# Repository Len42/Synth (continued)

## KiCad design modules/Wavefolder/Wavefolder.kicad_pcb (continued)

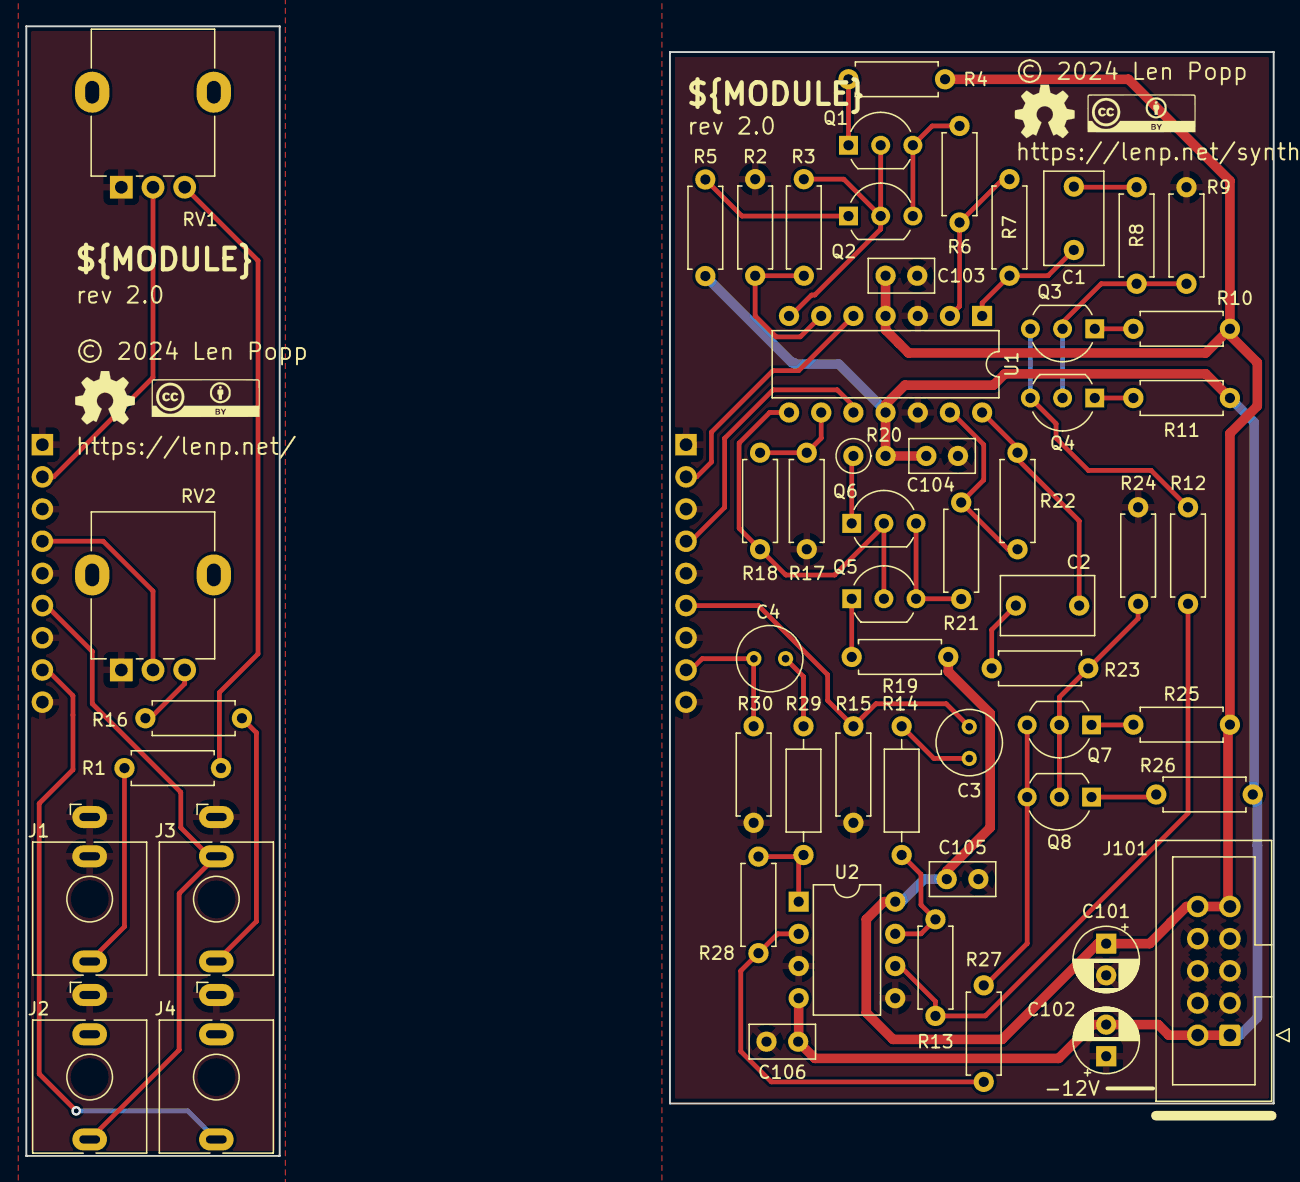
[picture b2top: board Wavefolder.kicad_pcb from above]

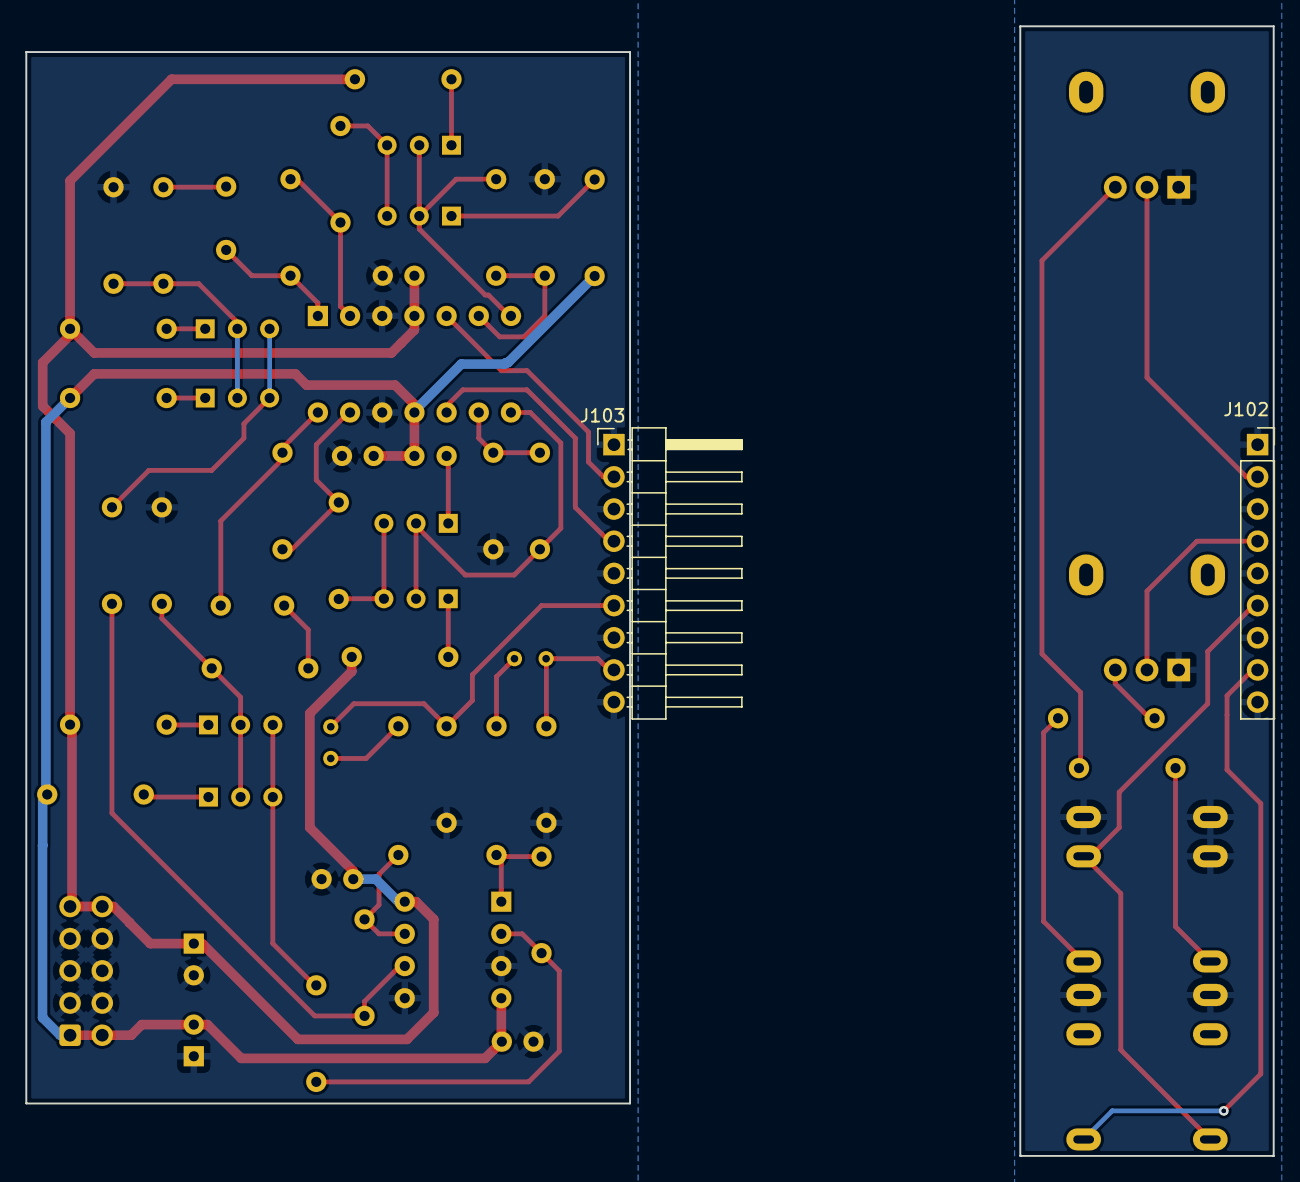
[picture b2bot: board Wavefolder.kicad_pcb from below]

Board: 2 copper layers, 98.5 x 89.2 mm, 63 parts (2 on the bottom side), 41 nets.

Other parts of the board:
G1, G2: Logo_CC_BY
G3, G4: Logo_OSHW

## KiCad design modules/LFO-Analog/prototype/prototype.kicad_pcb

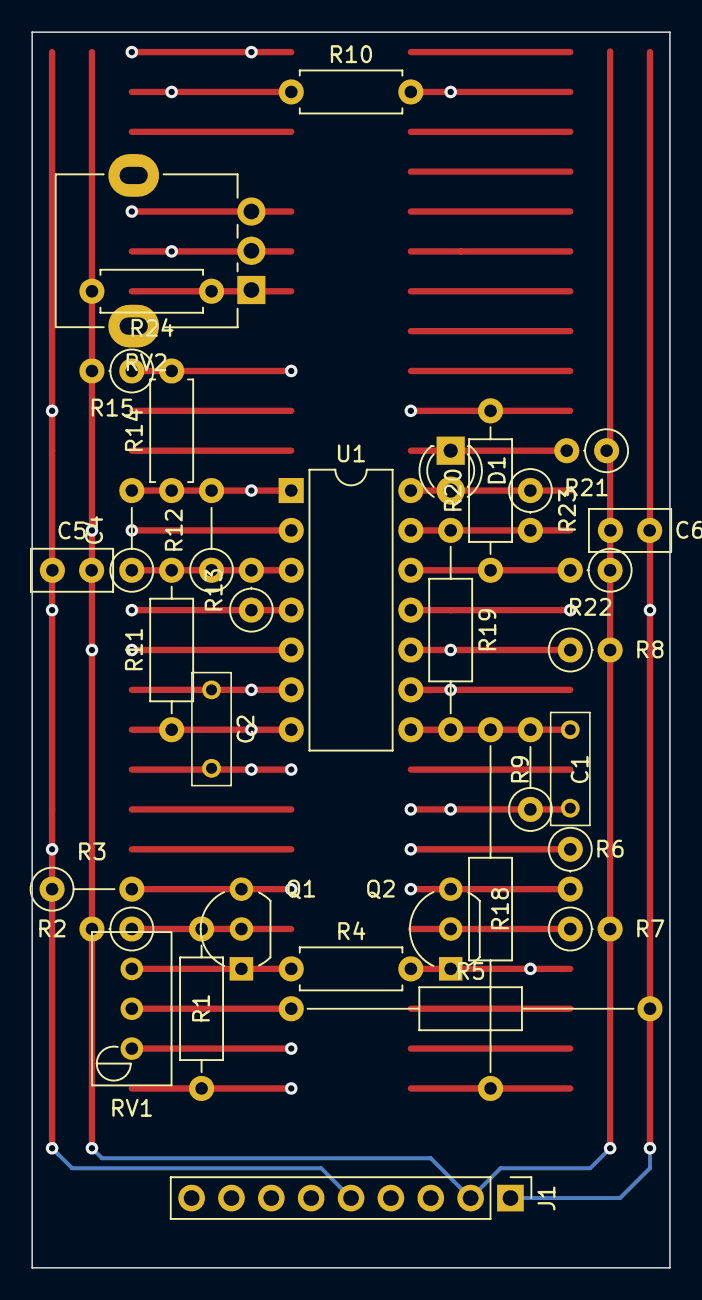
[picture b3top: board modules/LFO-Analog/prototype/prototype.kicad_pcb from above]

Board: 6 copper layers, 40.6 x 78.7 mm, 34 parts (0 on the bottom side), 22 nets.

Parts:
C1, C2: 3N3; C_Rect_Kemet_L7.2mm_W2.5mm_P5mm
C4: 47P; SB_Gen_2
C5, C6: 100N; C_Disc_D5.0mm_W2.5mm_P2.50mm
D1: LED; LED_D3.0mm_Clear
J1: Conn_01x09; PinHeader_1x09_P2.54mm_Vertical
Q1, Q2: 2N3904; TO-92_Inline_Wide
R1, R11: 100K; SB_Gen_4
R2: 2K2; SB_Gen_1
R3: 10K; SB_Gen_2
R4, R24: 220R; R_Axial_DIN0207_L6.3mm_D2.5mm_P7.62mm_Horizontal
R5: 68K; SB_Gen_9
R6, R15: 10K; SB_Gen_1
R7: 470R; SB_Gen_1
R8, R22: 36K; SB_Gen_1
R9: 36K; SB_Gen_2
R10: 300K; R_Axial_DIN0207_L6.3mm_D2.5mm_P7.62mm_Horizontal
R12: 200K; SB_Gen_2
R13: 4M7; SB_Gen_1
R14: 11K; R_Axial_DIN0207_L6.3mm_D2.5mm_P7.62mm_Horizontal
R18: 1K; SB_Gen_9
R19: 220K; SB_Gen_5
R20: 220K; SB_Gen_4
R21: 1K; SB_Gen_1
R23: 100K; SB_Gen_1
RV1: 25K; Potentiometer_Bourns_3296W_Vertical
RV2: 100K; Potentiometer_Alpha_RD901F-40-00D_Single_Vertical
U1: TL074; DIP-14_W7.62mm

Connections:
+12V: C5.1, J1.5, R3.1, R6.1, R13.1, R20.2, U1.4 (V+)
-12V: C6.2, J1.1, R5.2, U1.11 (V-)
GND: C5.2, C6.1, J1.2, R2.2, R7.2, R8.2, R15.2, R21.1, R22.1, R24.2, U1.2 (-), U1.5 (+)
IN: C2.2, J1.4, R1.2, R11.1, U1.7
unnamed: C1.2, R9.2, R18.1, R19.2, U1.8
unnamed: C4.2, R12.2, R14.1, RV2.3, U1.1
unnamed: D1.2 (A), R23.1, U1.14
unnamed: D1.1 (K), R21.2
unnamed: Q1.2 (B), R1.1, R2.1
unnamed: C1.1, Q1.3 (C), R3.2, R9.1, U1.9 (-)
unnamed: Q1.1 (E), R4.1, RV1.3
unnamed: Q2.2 (B), R7.1
unnamed: Q2.3 (C), R6.2, R8.1, U1.10 (+)
unnamed: Q2.1 (E), R4.2, RV1.1
unnamed: R5.1, RV1.2
unnamed: R10.1, RV2.2
unnamed: R24.1, RV2.1
unnamed: C4.1, R11.2, R12.1, R13.2, U1.3 (+)
unnamed: C2.1, R10.2, U1.6 (-)
unnamed: R20.1, R22.2, U1.12 (+)
unnamed: R19.1, R23.2, U1.13 (-)
OUT-SQUARE: R14.2, R15.1

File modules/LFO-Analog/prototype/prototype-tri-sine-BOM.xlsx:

Ref | Qty | Value | Value2 | Note | Description | Datasheet | Manufacturer | ManuPartNum | Distributor1 | DistributorPartNum1 | DistributorPartLink1 | Distributor2 | DistributorPartNum2 | DistributorPartLink2 | Distributor3 | DistributorPartNum3 | DistributorPartLink3
C1 | 1 | 3N3 |  |  | Capacitor - Film
C5 C6 | 2 | 100N |  | IC decoupling | Capacitor - Ceramic - IC decoupling | https://product.tdk.com/system/files/dam/doc/product/capacit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 | TDK | FG18X7R1H104KNT06 | Mouser | 810-FG18X7R1H104KNT6 | https://www.mouser.ca/ProductDetail/810-FG18X7R1H104KNT6
Q1 Q2 | 2 | 2N3904 |  |  | Small Signal NPN Transistor, 0.2A Ic, 40V Vce, TO-92 | https://www.onsemi.com/pub/Collateral/2N3903-D.PDF | Central Semiconductor | 2N3904 PBFREE | Mouser | 610-2N3904 | https://www.mouser.ca/ProductDetail/Central-Semiconductor/2N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
R1 | 1 | 100K | 1%, 1/6 W |  | Resistor | https://www.mouser.ca/datasheet/2/447/YAGEO_MFR_datasheet_20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 | YAGEO | MFR-12* | Mouser | 603-MFR-12* | https://www.mouser.ca/c/?m=YAGEO&power+rating=166+mW+(1%2f6+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
R2 | 1 | 2K2 | 1%, 1/6 W |  | Resistor | https://www.mouser.ca/datasheet/2/447/YAGEO_MFR_datasheet_20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 | YAGEO | MFR-12* | Mouser | 603-MFR-12* | https://www.mouser.ca/c/?m=YAGEO&power+rating=166+mW+(1%2f6+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
R3 R6 | 2 | 10K | 1%, 1/6 W |  | Resistor | https://www.mouser.ca/datasheet/2/447/YAGEO_MFR_datasheet_20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 | YAGEO | MFR-12* | Mouser | 603-MFR-12* | https://www.mouser.ca/c/?m=YAGEO&power+rating=166+mW+(1%2f6+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
R4 | 1 | 220R | 1%, 1/6 W |  | Resistor | https://www.mouser.ca/datasheet/2/447/YAGEO_MFR_datasheet_20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 | YAGEO | MFR-12* | Mouser | 603-MFR-12* | https://www.mouser.ca/c/?m=YAGEO&power+rating=166+mW+(1%2f6+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
R5 | 1 | 68K | 1%, 1/6 W |  | Resistor | https://www.mouser.ca/datasheet/2/447/YAGEO_MFR_datasheet_20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 | YAGEO | MFR-12* | Mouser | 603-MFR-12* | https://www.mouser.ca/c/?m=YAGEO&power+rating=166+mW+(1%2f6+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
R7 | 1 | 470R | 1%, 1/6 W |  | Resistor | https://www.mouser.ca/datasheet/2/447/YAGEO_MFR_datasheet_20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 | YAGEO | MFR-12* | Mouser | 603-MFR-12* | https://www.mouser.ca/c/?m=YAGEO&power+rating=166+mW+(1%2f6+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
R8 R9 | 2 | 36K | 1%, 1/6 W |  | Resistor | https://www.mouser.ca/datasheet/2/447/YAGEO_MFR_datasheet_20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 | YAGEO | MFR-12* | Mouser | 603-MFR-12* | https://www.mouser.ca/c/?m=YAGEO&power+rating=166+mW+(1%2f6+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
RV1 | 1 | 25K |  |  | Trim-potentiometer | https://www.mouser.ca/datasheet/2/54/3296-776415.pdf | Bourns | 3296X-* | Mouser | 652-3296Z-* | https://www.mouser.ca/c/passive-components/potentiometers-tr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
U1 | 1 | TL074 |  |  | Quad Low-Noise JFET-Input Operational Amplifiers, DIP-14/SOIC-14 | http://www.ti.com/lit/ds/symlink/tl071.pdf | Texas Instruments | TL074BCN | Mouser | 595-TL074BCN | https://www.mouser.ca/ProductDetail/?qs=vxEfx8VrU7BHurOY5iQd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

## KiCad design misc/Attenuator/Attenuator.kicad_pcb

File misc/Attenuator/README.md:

# Attenuator

_Eurorack attenuator dongle_

## Features
- Passive attenuator, approximately -20 dB
- A small dongle that can be patched between modules or devices
- Bidirectional - plug it in either way around!

## Notes
I made two of these small attenuator dongles for my Eurorack system because I kept running into situations where I want to knock down the signal level by a large amount. I have a fancy [attenuverter module](../../modules/Attenuverter/) but I just wanted something small and simple that would leave the attenuverter free for more important jobs.

<div style="float:right">

</div>

My particular reasons for using this attenuator are:
* _Using a tuner (or other external device)_ - I have a [tuner](https://www.korg.com/caen/products/tuners/ot_120/) that has trouble with the signal level straight out of a Eurorack VCO, so I keep one of these attenuators plugged into the tuner.
* _Bad design choices_ - I made the pitch mod inputs on my oscillator modules way too sensitive. Even though there's an attenuator control on the input, it's hard to get a reasonable vibrato when I patch in an LFO. Sending the LFO through this attenuator gives a much better range of adjustment on the pitch mod input, for most purposes.

The device is assembled on a small piece of stripboard PCB. See the attached layout diagram.

Please note that I am a hobbyist, not a trained electronics engineer. No guarantees!

## Software Used

* [KiCad](https://www.kicad.org/) 7.0.8

<hr /><div><div style="float:left; padding-right:10px;"></div><div style="padding-left:10px;"><br />© 2024 Len Popp CC BY<br />This work is licensed under a <a rel="license" href="http://creativecommons.org/licenses/by/4.0/">Creative Commons Attribution 4.0 International License</a>.</div></div>

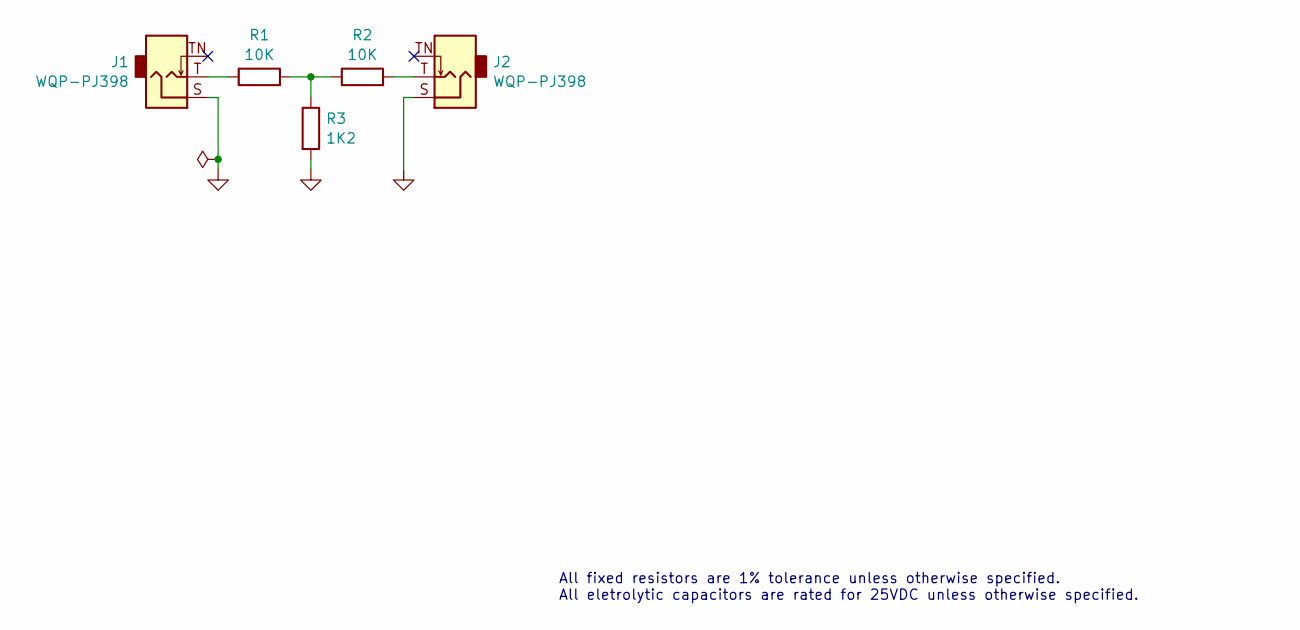
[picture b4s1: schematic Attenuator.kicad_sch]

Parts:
J1, J2: WQP-PJ398; Jack_3.5mm_BB_QingPu_WQP-PJ398SM; ManufacturerPartNum PJ398SM / WQP518MA
R1: 10K; SB_Gen_1; ManufacturerPartNum MFR-12FTF52-10K
R2: 10K; R_Axial_DIN0207_L6.3mm_D2.5mm_P10.16mm_Horizontal; ManufacturerPartNum MFR-12FTF52-10K
R3: 1K2; R_Axial_DIN0207_L6.3mm_D2.5mm_P7.62mm_Horizontal; ManufacturerPartNum MFR-12FTF52-1K2

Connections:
GND: J1.S, J2.S, R3.2
unnamed: J1.T, R1.1
unnamed: J2.T, R2.2
unnamed: R1.2, R2.1, R3.1

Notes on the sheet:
All fixed resistors are 1% tolerance unless otherwise specified. All eletrolytic capacitors are rated for 25VDC unless otherwise specified.

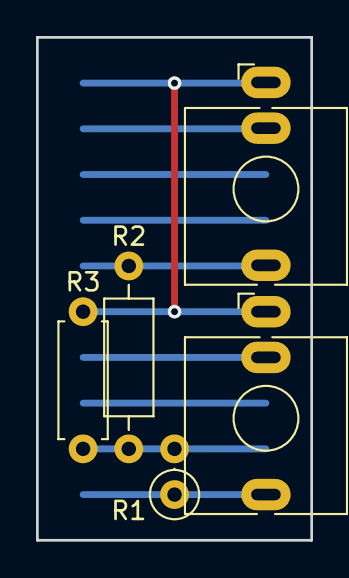
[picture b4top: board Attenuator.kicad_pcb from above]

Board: 2 copper layers, 15.2 x 27.9 mm, 5 parts (0 on the bottom side), 4 nets.

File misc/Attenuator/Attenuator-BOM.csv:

Ref,Qty,Value,Value2,Note,Description,Datasheet,Manufacturer,ManuPartNum,Distributor1,DistributorPartNum1,DistributorPartLink1,Distributor2,DistributorPartNum2,DistributorPartLink2,Distributor3,DistributorPartNum3,DistributorPartLink3
"J1 J2","2","WQP-PJ398","","","Audio Jack, 2 Poles (Mono / TS), Switched T Pole (Normalling), QingPu / Thonkiconn","http://www.qingpu-electronics.com/en/products/WQP-PJ398SM-362.html","QingPu / Thonk","PJ398SM / WQP518MA","Thonk","PJ398SM","https://www.thonk.co.uk/shop/thonkiconn/","SynthCube","WQP518MA","https://synthcube.com/cart/3-5mm-euro-jacks","Adafruit","4031","https://www.adafruit.com/product/4031"
"R1 R2","2","10K","1%, 1/6 W","","Resistor","https://www.mouser.ca/datasheet/2/447/YAGEO_MFR_datasheet_20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","YAGEO","MFR-12FTF52-10K","Mouser","603-MFR-12FTF52-10K","https://www.mouser.ca/ProductDetail/YAGEO/MFR-12FTF52-10K?qs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","","","","","",""
"R3","1","1K2","1%, 1/6 W","","Resistor","https://www.mouser.ca/datasheet/2/447/YAGEO_MFR_datasheet_20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","YAGEO","MFR-12FTF52-1K2","Mouser","603-MFR-12FTF52-1K2","https://www.mouser.ca/ProductDetail/YAGEO/MFR-12FTF52-1K2?qs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","","","","","",""

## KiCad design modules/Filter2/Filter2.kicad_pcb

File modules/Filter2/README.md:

# Filter2 - Dual Filter Module

## 10HP Eurorack Module

_Two variable formant or whatever filters_

### Features
- Two separate multi-mode filters (low/high/band-pass)
- _Not_ voltage controlled. Use your fingers! 👌
- Frequency, resonance, and gain controls
- Channel 1 input is normalled to channel 2

### Notes
This module has two 2-pole state-variable filters, switchable between lowpass, highpass, and bandpass. They can be used for for tone shaping, formant synthesis, or EQ. By making them manually adjustable but not voltage-controlled, I was able to fit two filters into a 10 HP module using through-hole components. I just need lots of filters!

These filters do not self-oscillate at maximum resonance.

PCB layouts are provided in KiCad and gerber formats. A PCB layout for a drilled front panel (with no labels) is also included.

The PCBs that I used can be ordered from OSH Park. The designs are here:
- [Front panel](https://oshpark.com/shared_projects/P2GF37lL)
- [Controls board](https://oshpark.com/shared_projects/ycqpKJmS)
- [Main board](https://oshpark.com/shared_projects/lXygYNUP)

Please note that I am a hobbyist, not a trained electronics engineer. No guarantees!

### Acknowledgements

[Quad Bandpass, Parametric Equalizer - haraldswerk](https://www.haraldswerk.de/Filter/Bandpass_quad/Bandpass_quad.html)

### Software Used

* [KiCad](https://www.kicad.org/) 7.0.8

<hr /><div><div style="float:left; padding-right:10px;"></div><div style="xfloat:left; padding-left:10px;"><br />© 2024 Len Popp CC BY<br />This work is licensed under a <a rel="license" href="http://creativecommons.org/licenses/by/4.0/">Creative Commons Attribution 4.0 International License</a>.</div></div>

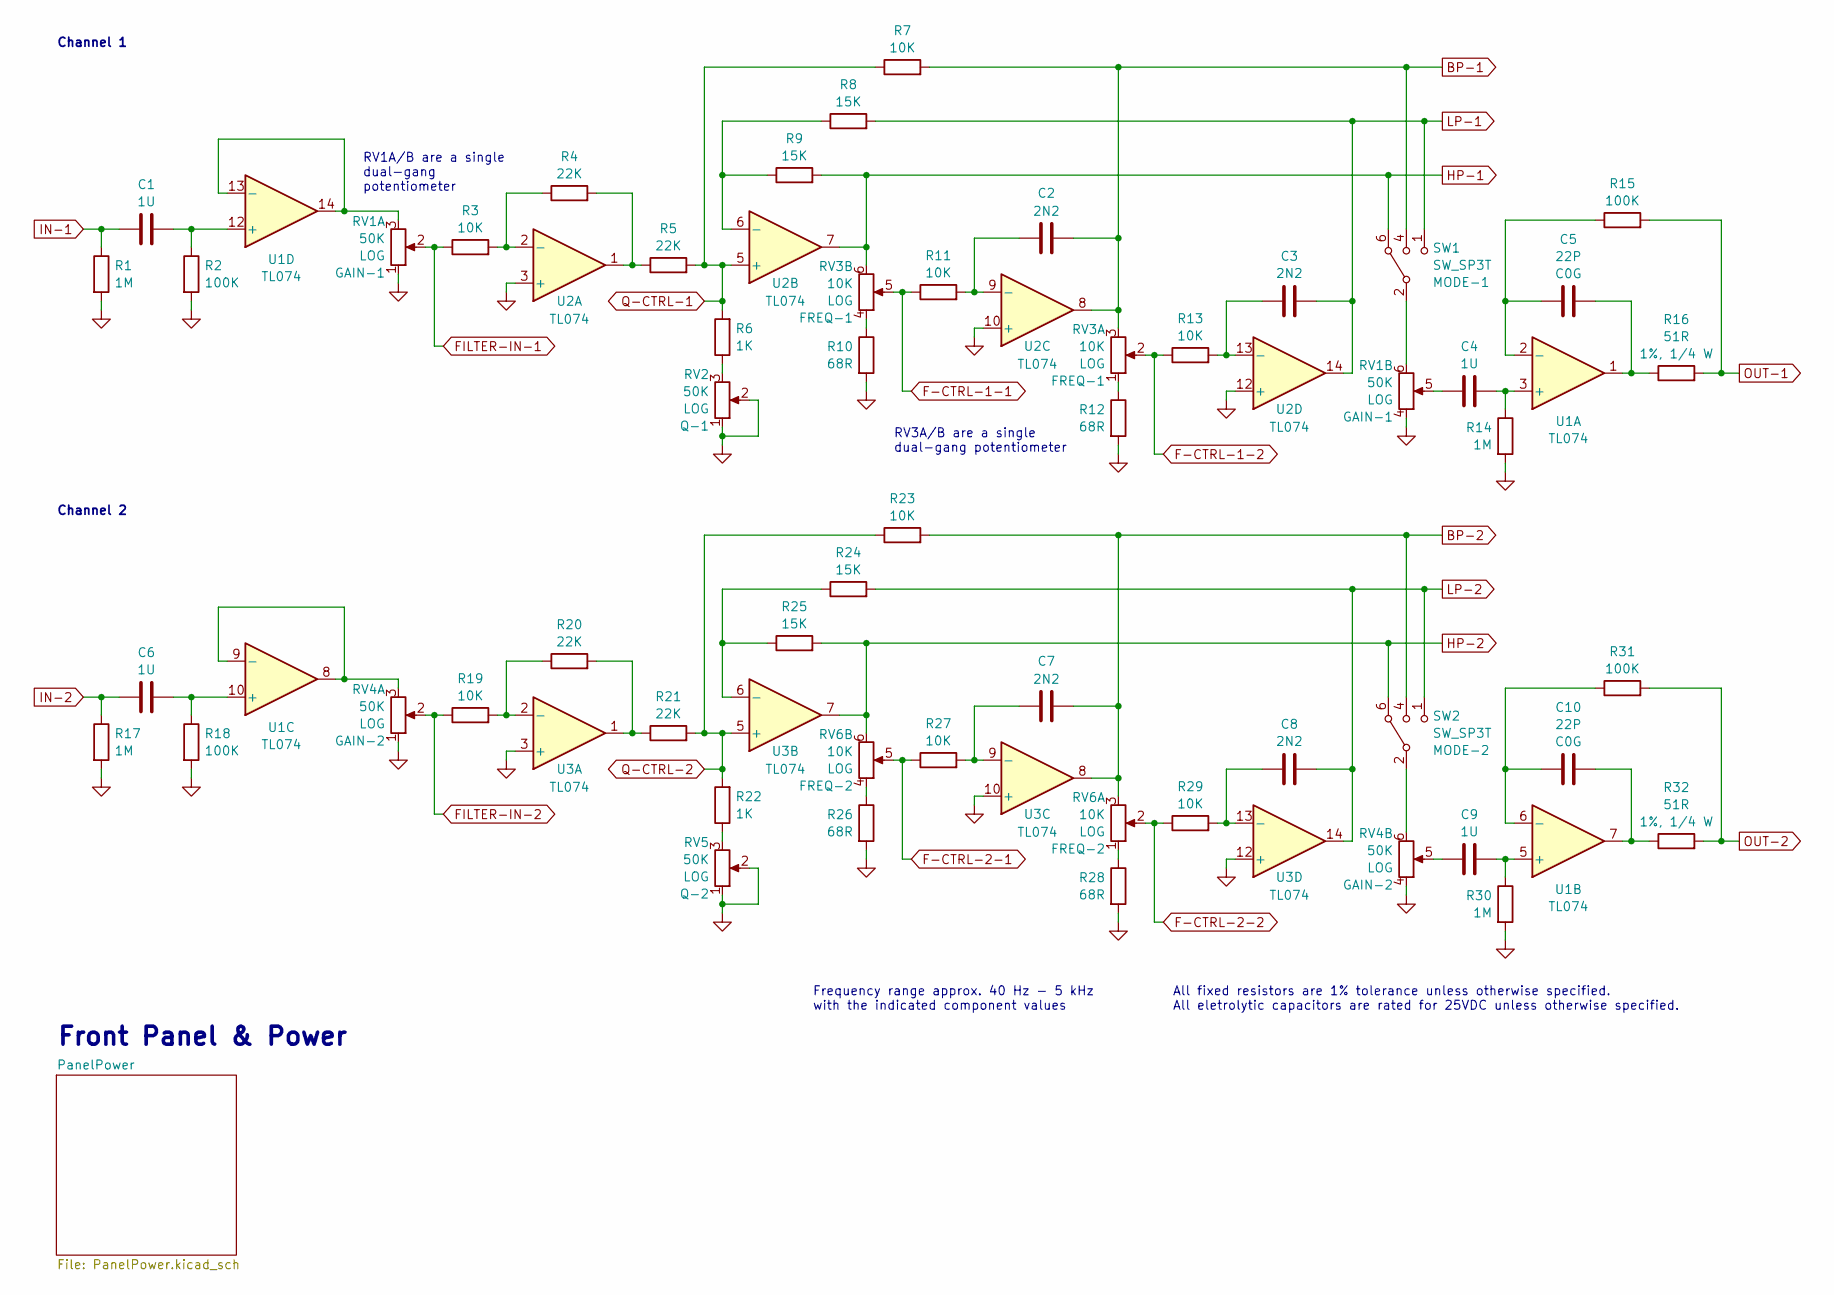
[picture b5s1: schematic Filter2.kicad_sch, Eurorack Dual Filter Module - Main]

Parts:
C1, C4, C6, C9: 1U; C_Rect_Kemet_L7.2mm_W2.5mm_P5mm; ManufacturerPartNum R82DC4100AA60K
C2, C3, C7, C8: 2N2; C_Rect_Kemet_L7.2mm_W2.5mm_P5mm; ManufacturerPartNum MMK5222J100J01L16.5TA18
C5, C10: 22P; C_Disc_D5.0mm_W2.5mm_P2.50mm; ManufacturerPartNum FG18C0G1H220JNT00
R1, R14, R17, R30: 1M; R_Axial_DIN0207_L6.3mm_D2.5mm_P7.62mm_Horizontal; ManufacturerPartNum MFR-12FTF52-1M
R2, R15, R18, R31: 100K; R_Axial_DIN0207_L6.3mm_D2.5mm_P7.62mm_Horizontal; ManufacturerPartNum MFR-12FTF52-100K
R3, R7, R11, R13, R19, R23, R27, R29: 10K; R_Axial_DIN0207_L6.3mm_D2.5mm_P7.62mm_Horizontal; ManufacturerPartNum MFR-12FTF52-10K
R4, R5, R20, R21: 22K; R_Axial_DIN0207_L6.3mm_D2.5mm_P7.62mm_Horizontal; ManufacturerPartNum MFR-12FTF52-22K
R6, R22: 1K; R_Axial_DIN0207_L6.3mm_D2.5mm_P7.62mm_Horizontal; ManufacturerPartNum MFR-12FTF52-1K
R8, R9, R24, R25: 15K; R_Axial_DIN0207_L6.3mm_D2.5mm_P7.62mm_Horizontal; ManufacturerPartNum MFR-12FTF52-15K
R10, R12, R26, R28: 68R; R_Axial_DIN0207_L6.3mm_D2.5mm_P7.62mm_Horizontal; ManufacturerPartNum MFR-12FTF52-68R
R16, R32: 51R; R_Axial_DIN0207_L6.3mm_D2.5mm_P10.16mm_Horizontal; ManufacturerPartNum MFR-25FBF52-51R
RV1, RV4: 50K; Potentiometer_Alpha_RD902F-40-00D_Dual_Vertical; ManufacturerPartNum RD902F-*
RV2, RV5: 50K; Potentiometer_Alpha_RD901F-40-00D_Single_Vertical; ManufacturerPartNum RD901F-*
RV3, RV6: 10K; Potentiometer_Alpha_RD902F-40-00D_Dual_Vertical; ManufacturerPartNum RD902F-*
SW1, SW2: SW_SP3T; SW_SP3T_A24JP; ManufacturerPartNum A24JP
U1, U2, U3: TL074; DIP-14_W7.62mm; ManufacturerPartNum TL074BCN

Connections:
BP-1: C2.2, R7.2, RV3.3, SW1.4, U2.8; also elsewhere on the board
BP-2: C7.2, R23.2, RV6.3, SW2.4, U3.8; also elsewhere on the board
F-CTRL-1-1: R11.1, RV3.5; also elsewhere on the board
F-CTRL-1-2: R13.1, RV3.2; also elsewhere on the board
F-CTRL-2-1: R27.1, RV6.5; also elsewhere on the board
F-CTRL-2-2: R29.1, RV6.2; also elsewhere on the board
FILTER-IN-1: R3.1, RV1.2; also elsewhere on the board
FILTER-IN-2: R19.1, RV4.2; also elsewhere on the board
GND: R1.2, R2.2, R10.2, R12.2, R14.2, R17.2, R18.2, R26.2, R28.2, R30.2, RV1.1, RV1.4, RV2.1, RV2.2, RV4.1, RV4.4, RV5.1, RV5.2, U2.3 (+), U2.10 (+), U2.12 (+), U3.3 (+), U3.10 (+), U3.12 (+); also elsewhere on the board
HP-1: R9.2, RV3.6, SW1.6, U2.7; also elsewhere on the board
HP-2: R25.2, RV6.6, SW2.6, U3.7; also elsewhere on the board
IN-1: C1.1, R1.1; also elsewhere on the board
IN-2: C6.1, R17.1; also elsewhere on the board
LP-1: C3.2, R8.2, SW1.1, U2.14; also elsewhere on the board
LP-2: C8.2, R24.2, SW2.1, U3.14; also elsewhere on the board
unnamed: C4.1, RV1.5
unnamed: C5.2, R16.1, U1.1
unnamed: C9.1, RV4.5
unnamed: C10.2, R32.1, U1.7
unnamed: R4.2, R5.1, U2.1
unnamed: R6.1, RV2.3
unnamed: R10.1, RV3.4
unnamed: R12.1, RV3.1
unnamed: R20.2, R21.1, U3.1
unnamed: R22.1, RV5.3
unnamed: R26.1, RV6.4
unnamed: R28.1, RV6.1
unnamed: RV1.6, SW1.2
unnamed: RV4.6, SW2.2
unnamed: C4.2, R14.1, U1.3 (+)
unnamed: C5.1, R15.1, U1.2 (-)
unnamed: C9.2, R30.1, U1.5 (+)
unnamed: C10.1, R31.1, U1.6 (-)
unnamed: C6.2, R18.1, U1.10 (+)
unnamed: RV4.3, U1.8, U1.9 (-)
unnamed: C1.2, R2.1, U1.12 (+)
unnamed: RV1.3, U1.13 (-), U1.14
unnamed: R3.2, R4.1, U2.2 (-)
unnamed: R8.1, R9.1, U2.6 (-)
unnamed: C2.1, R11.2, U2.9 (-)
unnamed: C3.1, R13.2, U2.13 (-)
unnamed: R19.2, R20.1, U3.2 (-)
unnamed: R24.1, R25.1, U3.6 (-)
unnamed: C7.1, R27.2, U3.9 (-)
unnamed: C8.1, R29.2, U3.13 (-)
OUT-1: R15.2, R16.2; also elsewhere on the board
OUT-2: R31.2, R32.2; also elsewhere on the board
Q-CTRL-1: R5.2, R6.2, R7.1, U2.5 (+); also elsewhere on the board
Q-CTRL-2: R21.2, R22.2, R23.1, U3.5 (+); also elsewhere on the board

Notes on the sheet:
All fixed resistors are 1% tolerance unless otherwise specified. All eletrolytic capacitors are rated for 25VDC unless otherwise specified.
Frequency range approx. 40 Hz - 5 kHz with the indicated component values
RV1A/B are a single dual-gang potentiometer
Channel 2
RV3A/B are a single dual-gang potentiometer
Channel 1
Front Panel & Power

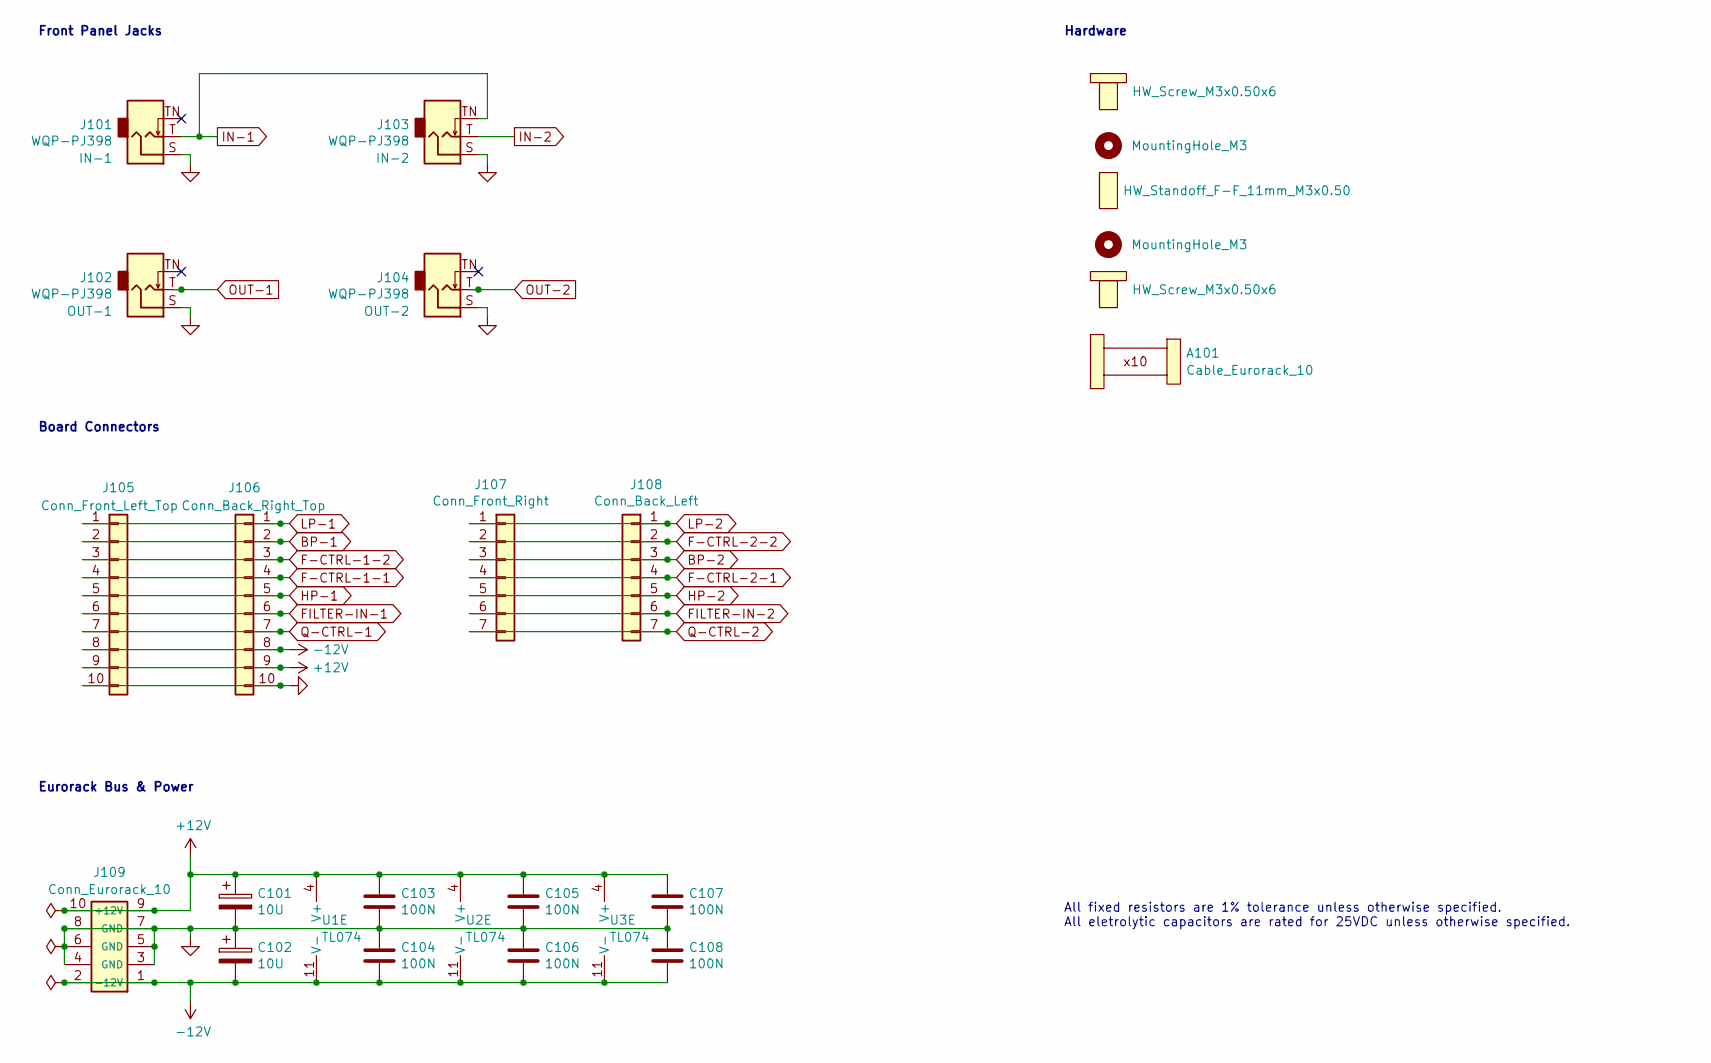
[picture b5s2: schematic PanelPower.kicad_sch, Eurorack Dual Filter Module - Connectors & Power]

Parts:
A101: Cable_Eurorack_10; NoFootprint
C101, C102: 10U; CP_Radial_D5.0mm_P2.50mm; ManufacturerPartNum ECE-A1VKS100I
C103, C104, C105, C106, C107, C108: 100N; C_Disc_D5.0mm_W2.5mm_P2.50mm; ManufacturerPartNum FG18X7R1H104KNT06
H101, H105: HW_Screw_M3x0.50x6
H102, H104: MountingHole_M3; MountingHole_PCB_3.2mm_M3
H103: HW_Standoff_F-F_11mm_M3x0.50; ManufacturerPartNum 05.03.111
J101, J102, J103, J104: WQP-PJ398; Jack_3.5mm_QingPu_WQP-PJ398SM_Vertical; ManufacturerPartNum PJ398SM / WQP518MA
J105: Conn_Front_Left_Top; PinSocket_1x10_P2.54mm_Vertical
J106: Conn_Back_Right_Top; PinHeader_1x10_P2.54mm_Vertical
J107: Conn_Front_Right; PinSocket_1x07_P2.54mm_Vertical
J108: Conn_Back_Left; PinHeader_1x07_P2.54mm_Vertical
J109: Conn_Eurorack_10; IDC-Header-Eurorack-10-TH; ManufacturerPartNum 61201021621
U1, U2, U3: TL074; DIP-14_W7.62mm; ManufacturerPartNum TL074BCN

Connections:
+12V: C101.1, C103.1, C105.1, C107.1, J105.9, J106.9, J109.9 (+12V), J109.10, U1.4 (V+), U2.4 (V+), U3.4 (V+)
-12V: C102.2, C104.2, C106.2, C108.2, J105.8, J106.8, J109.1 (-12V), J109.2, U1.11 (V-), U2.11 (V-), U3.11 (V-)
BP-1: J105.2, J106.2; also elsewhere on the board
BP-2: J107.3, J108.3; also elsewhere on the board
F-CTRL-1-1: J105.4, J106.4; also elsewhere on the board
F-CTRL-1-2: J105.3, J106.3; also elsewhere on the board
F-CTRL-2-1: J107.4, J108.4; also elsewhere on the board
F-CTRL-2-2: J107.2, J108.2; also elsewhere on the board
FILTER-IN-1: J105.6, J106.6; also elsewhere on the board
FILTER-IN-2: J107.6, J108.6; also elsewhere on the board
GND: C101.2, C102.1, C103.2, C104.1, C105.2, C106.1, C107.2, C108.1, J101.S, J102.S, J103.S, J104.S, J105.10, J106.10, J109.3 (GND), J109.4, J109.5 (GND), J109.6, J109.7 (GND), J109.8; also elsewhere on the board
HP-1: J105.5, J106.5; also elsewhere on the board
HP-2: J107.5, J108.5; also elsewhere on the board
IN-1: J101.T, J103.TN; also elsewhere on the board
IN-2: J103.T; also elsewhere on the board
LP-1: J105.1, J106.1; also elsewhere on the board
LP-2: J107.1, J108.1; also elsewhere on the board
OUT-1: J102.T; also elsewhere on the board
OUT-2: J104.T; also elsewhere on the board
Q-CTRL-1: J105.7, J106.7; also elsewhere on the board
Q-CTRL-2: J107.7, J108.7; also elsewhere on the board

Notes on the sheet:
Hardware
All fixed resistors are 1% tolerance unless otherwise specified. All eletrolytic capacitors are rated for 25VDC unless otherwise specified.
Front Panel Jacks
Board Connectors
Eurorack Bus & Power

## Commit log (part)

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2022-11-01 FX: Update footprints for holes on front panel
2022-11-01 FX: update gerber files
2022-11-02 FX - minor schematic update
2022-11-02 FX - remove unnecessary files
2022-11-02 FX: docs - wip
2022-11-03 FX - Digital effects module (#42)
    FX - Digital effects module
2022-11-03 Buff-Mult: invisible updates to schematic & PCB layout
2022-11-03 Buff-Mult: add PCB layout image
2022-11-10 Buff-Mult: Remove temporary files
2022-11-10 Buff-Mult: update README
2022-11-10 Bus-Driver: Improved accuracy
2022-11-10 Buff-Mult: update schematic PDF
2022-11-10 Buff-Mult - Improved precision (#43)
    Improved precision in the output stage
2022-11-10 Buff-Mult: Remove temporary files (#45)
2022-11-10 Bus-Driver: Improved accuracy (#44)
2022-11-10 Adder: PCB layout image
2022-11-11 Adder: remove unnecessary file
2022-11-11 VCF-SV: State-variable VCF - initial commit
2022-11-12 Adder: Change the design to use regular-precision components by default
2022-11-12 Adder: update schematic PDF
2022-11-12 Adder: Delete unnecessary files
2022-11-13 Adder: add photo to README
2022-11-13 Adder - docs
2022-11-13 Adder (#46)
    Adder module
2022-11-14 Mixer1 - initial commit
2022-11-14 Mixer1 - wip
2022-11-15 Mixer1 - front panel - wip
2022-11-15 Mixer1: gerber files
2022-11-16 Mixer1: BOM - wip
2022-11-16 Mixer1: BOM - done
2022-11-17 VCF-SV: wip
2022-11-18 VCF-SV: prptotype - wip
2022-11-19 VCF-SV: prototype - wip
2022-11-23 VCF-4P: Changed a resistor for better frequency CV tracking
2022-11-23 VCF-4P: better frequency CV tracking (#47)
    VCF-4P: Changed a resistor for better frequency CV tracking
2022-11-25 VCF-SV: proto - wip
2022-11-27 VCF-SV: proto - update pcb.png
2022-12-01 VCF-SV: update README
2022-12-02 VCF-SV: change some refdes
2022-12-02 VCF-SV: fix PCB silkscreen
2022-12-06 VCF-SV: proto - notch output wip
2022-12-06 VCF-SV: proto - HP/LP/notch output
2022-12-09 VCF-SV: proto
2022-12-09 VCF-SV: update from prototype - wip
2022-12-10 VCF-SV: update from prototype and finish pcb layout
2022-12-10 VCF-SV: BOM
2022-12-10 VCF-SV: corrections
2022-12-10 VCF-SV: tweaks
2022-12-10 VCF-SV: don't have to buy a hole
2022-12-11 VCF-SV: front panel
2022-12-11 VCF-SV: README
2022-12-12 VCF-SV: adjust control positions
2022-12-12 VCF-SV: gerber files
2022-12-13 Doc: Bus CV & gate
2022-12-14 Doc: Eurorack bus & CV (#48)
    Doc: Bus CV & gate
2022-12-14 Doc: Bus CV & gate - markdown fubar
2022-12-14 Doc bus cv (#49)
    Doc: Bus CV & gate
2022-12-14 Doc bus cv (#50)
    Doc: Bus CV & gate
2022-12-14 Doc bus cv (#51)
    Doc: Bus CV & gate
2022-12-14 Doc bus cv (#52)
    Doc: Bus CV & gate
2022-12-22 Mixer1: fix front panel footprints
2022-12-22 Mixer1: - clean up schematic - fix output jack connection
2022-12-22 Mixer1: schematic.pdf, pcb.png
2022-12-25 Mixer1: Update document properties
2022-12-25 Mixer1: README
2022-12-25 Mixer1: schematic.pdf
2022-12-25 Mixer1: delete unnecessary files
2022-12-25 Mixer1: update docs/index.md
2022-12-25 Mixer1 module (#53)
    Mixer1 module
2022-12-26 Mixer1 - add a photo
2022-12-26 Mixer1 photo (#54)
    Mixer1 photo
2023-01-08 VCF-SV: schematic & pcb images
2023-01-10 VCF-SV: Adjust a couple of resistor values
2023-01-11 VCF-SV: Documentation
2023-01-11 VCF-SV: Remove a bunch of files
2023-01-12 VCF-SV: gerber disclaimer
2023-01-12 VCF-SV filter module (#55)
    VCF-SV state-variable filter module
2023-01-26 update some snippets
2023-01-26 Update some docs (#56)
    Update some docs
2023-01-30 edit panels.md
2023-07-04 edit firmware-programming.md
2023-07-23 docs: add Dexy to the list of modules
2023-07-23 Doc update (#58)
    Add Dexy to the list of modules
2023-10-01 doc: update photos
2023-10-07 Switches module - wip
2023-10-07 Switches module - 2nd try
2023-10-07 Switches module - update KiCAD
2023-10-08 Switches module - add breadboard prototype
2023-10-08 Switches module - prototype wip
2023-10-08 Switches module - add JFET prototype
2023-10-10 Switches module - flipflop test
2023-10-10 Switches module - flipflop testing - wip
2023-10-10 Switches module - flipflop testing - new prototype
2023-10-11 Switches module - flipflop testing - it works!
2023-10-11 Switches module - prototype - wip
2023-10-11 Switches module - combined prototype
2023-10-12 Switches - module design - wip
2023-10-13 Switches - PCB layout - wip
2023-10-14 Switches - PCB layout - routing done
2023-10-14 Switches - PCB layout, BOM - wip
2023-10-14 Switches - PCB layout tweaks
2023-10-15 Switches - BOM
2023-10-15 Switches - schematic notes
2023-10-15 Switches - README.md wip
2023-10-15 Switches - front panel - wip
2023-10-16 Switches - front panel
2023-10-17 Switches - panel graphics
2023-10-17 Switches: - rename a file - add a standoff - PCB layout tweaks
2023-10-17 Switches - BOM update
2023-10-18 Switches - gerber files
2023-10-18 Switches - gerber files - corrections
2023-10-18 Switches - README
2023-10-19 Switches - re-arrange schematic p. 3
2023-10-19 Switches - schematic PDF
2023-10-19 Switches - schematic update
2023-10-29 Switches - temp partial PCB layout
2023-10-30 Switches - pcb.png
2023-11-01 Switches - README.md
2023-11-02 Switches - remove unpublished files
2023-11-02 Switches module (#59)
    Switches - 4-channel muting module
2023-11-02 doc update
2023-12-06 Filter2 prototype - wip
2023-12-07 Filter2 prototype
2023-12-08 Filter2 prototype & simulation
2023-12-08 Filter2 prototype BOM
2023-12-08 Filter2 prototype simulation
2023-12-09 Filter2 prototype - add 3-way switch
2023-12-10 Filter2 - wip
2023-12-10 fix REFDES
2023-12-10 Filter2 - second channel - wip
2023-12-11 Filter2 - BOM
2023-12-11 add Kicad lock files to .gitignore
2023-12-11 Filter2 - silkscreen cleanup
2023-12-11 Filter2 - PCB layout tweaks
2023-12-11 Filter2 - front panel; PCB tweaks
2023-12-11 Filter2 - README wip
2023-12-11 Filter2 - normalled inputs
2023-12-11 Filter2 - README
2023-12-12 Filter2 - schematic notes
2023-12-13 Filter2 - prototype tweaks
2023-12-13 Filter2 - curvy tracks
2023-12-13 Filter2 - simulate different component values
2023-12-14 Filter2 prototype - change some component values
2023-12-14 Filter2 prototype - layout tweaks
2023-12-14 Filter2 prototype - layout tweaks and remove switch
2023-12-15 Filter2 - adjust component values for better frequency range
2023-12-15 Filter2 prototype - use a big pot for frequency
2023-12-15 Filter2 prototype - change a footprint
2023-12-20 Filter2: BOM - wip
2023-12-20 Filter2: README - wip
2023-12-22 Filter2: verify front panel positions
2023-12-22 Filter2: add a note to a symbol
2023-12-22 Filter2: BOM
2023-12-23 Filter2: switch-test tester
2023-12-23 Filter2: add a note
2023-12-24 Filter2: gerber files
2023-12-24 Filter2: schematic tweak
2023-12-26 Filter2: schematic PDF
2024-01-30 Filter2: README
2024-01-30 Filter2: update last-modified date
2024-01-30 Filter2: remove non-essential files
2024-01-31 Filter2 module (#60)
    Filter2 module
2024-03-21 ignore some more files
2024-03-21 Documentation: Change links to point to lenp.net
2024-03-21 docs: test link
2024-03-21 Documentation: Add HTML redirects to the new site
2024-03-21 Documentation: Remove .md files that have been replaced by redirects
2024-03-21 Docs moved to new site (#61)
    Docs are being moved from GitHub Pages to lenp.net
2024-03-21 Docs are being moved from GitHub Pages to lenp.net
2024-03-21 add a missing README file
2024-03-22 docs: restore a photo that was removed
2024-04-02 Attenuator dongle - wip
2024-04-02 Attenuator dongle - README
2024-04-03 Attenuator (#62)
    Attenuator dongle
2024-04-05 Munger re-design - move old files out of the way temporarily
2024-04-05 Munger re-design - add new design files
2024-04-05 Munger re-design - schematic done, PCB started
2024-04-05 Munger re-design - PCB wip
2024-04-05 Munger re-design - README
2024-04-06 Munger re-design - PCB layout mostly done
2024-04-06 Munger re-design - PCB done
2024-04-06 Munger re-design - remove unused schematic sheet
2024-04-06 Munger re-design - Front panel PCB
2024-04-06 Munger re-design - Front panel PCB - wip
2024-04-06 Gerber files
2024-04-06 Munger re-design - ignore some local files
2024-04-06 Munger re-design - Gerber files
2024-04-06 Munger re-design - BOM - wip
2024-04-07 Munger re-design - BOM
2024-04-08 Envelope changes: initial testing
2024-04-09 Envelope changes: testing
2024-04-10 Envelope changes: Lengthened decay & release
2024-04-10 Envelope changes: testing & debugging
2024-04-10 Envelope changes: slower rates
2024-04-10 Envelope changes: cleanup
2024-04-10 Envelope changes: remove a temp file
2024-04-10 Envelope2 firmware changes (#63)
    Lengthened attack, decay, and release times (especially in logarithmic mode), and cleaned up the code a bit.
2024-04-19 Munger re-design - schematic.pdf
2024-04-24 Munger re-design - fix KiCad project info
2024-04-26 LFO-Analog: Project skeleton and prototype wip
2024-04-27 LFO-Analog: prototype wip
2024-04-28 LFO-Analog: prototype LED
2024-04-30 LFO-Analog: prototype - working!
2024-05-01 LFO-Analog: schematic - pretty much done
2024-05-01 LFO-Analog: PCB - wip
2024-05-02 Munger re-design - README.md
2024-05-02 Munger re-design - rename old directory
2024-05-02 Wavefolder v2 (#64)
    Wavefolder version 2 - custom PCB
2024-05-03 LFO-Analog: PCB - layout done
2024-05-03 LFO-Analog: BOM - wip
2024-05-04 remove an unnecessary file
2024-05-04 remove an unnecessary file (#65)
    remove an unnecessary file
2024-05-04 LFO-Analog: BOM testing
2024-05-04 LFO-Analog: BOM testing - it works!
2024-05-04 LFO-Analog: BOM testing - update PCB fields
2024-05-04 LFO-Analog: BOM testing - update some fields
2024-05-04 LFO-Analog: update README.md
2024-05-04 LFO-Analog: BOM testing - Remove old BOM files
2024-05-04 LFO-Analog: BOM - done
2024-05-05 LFO-Analog: schematic tweaks
2024-05-05 LFO-Analog: front panel PCB
2024-05-05 LFO-Analog: update the date
2024-05-06 LFO-Analog: misc little things
2024-05-06 LFO-Analog: change caps for different frequency range
2024-05-06 LFO-Analog: update BOM
2024-05-06 update README for LFO-Analog and LFO-DigiVC
2024-05-06 LFO-Analog: more BOM wip
2024-05-07 LFO-Analog: BOM updated
2024-05-10 LFO-Analog: Update dates & export schematic.pdf
2024-05-10 LFO-Analog: Gerber files
2024-05-13 LFO-Analog: ignore some files
2024-05-28 LFO-Analog: README
2024-05-28 LFO-Analog: Remove unnecessary files
2024-05-28 Dual Analog LFO (#66)
    Dual analog LFO module
2024-06-22 Attenuator: Add schematic.png
2024-06-30 Switches - fix a typo in the schematic
2024-06-30 Switches typo (#67)
    Switches - fix a typo in the schematic
2024-07-15 Power-Supply: update stripboard layout to match the board as built
2024-07-16 Power supply update (#68)
    Power-Supply: update stripboard layout to match the board as built
2024-11-27 Wavefolder: Fix a dead link in README
